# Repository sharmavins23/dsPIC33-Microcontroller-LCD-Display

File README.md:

# DSPIC33 Microcontroller with LCD Display

This project is a schematic and PCB layout of the dsPIC33 EP64 MC502
microcontroller, as well as an implementation of the LCD display and an LCD
display library.

## Schematic

The following is the circuit schematic.

## PCB Layout

The following is the PCB layout.

# License TL;DR

This project is distributed under the MIT license. This is a paraphrasing of a
[short summary](https://tldrlegal.com/license/mit-license).

This license is a short, permissive software license. Basically, you can do
whatever you want with this software, as long as you include the original
copyright and license notice in any copy of this software/source.

## What you CAN do:

-   You may commercially use this project in any way, and profit off it or the
    code included in any way;
-   You may modify or make changes to this project in any way;
-   You may distribute this project, the compiled code, or its source in any
    way;
-   You may incorporate this work into something that has a more restrictive
    license in any way;
-   And you may use the work for private use.

## What you CANNOT do:

-   You may not hold me (the author) liable for anything that happens to this
    code as well as anything that this code accomplishes. The work is provided
    as-is.

## What you MUST do:

-   You must include the copyright notice in all copies or substantial uses of
    the work;
-   You must include the license notice in all copies or substantial uses of the
    work.

If you're feeling generous, give credit to me somewhere in your projects.

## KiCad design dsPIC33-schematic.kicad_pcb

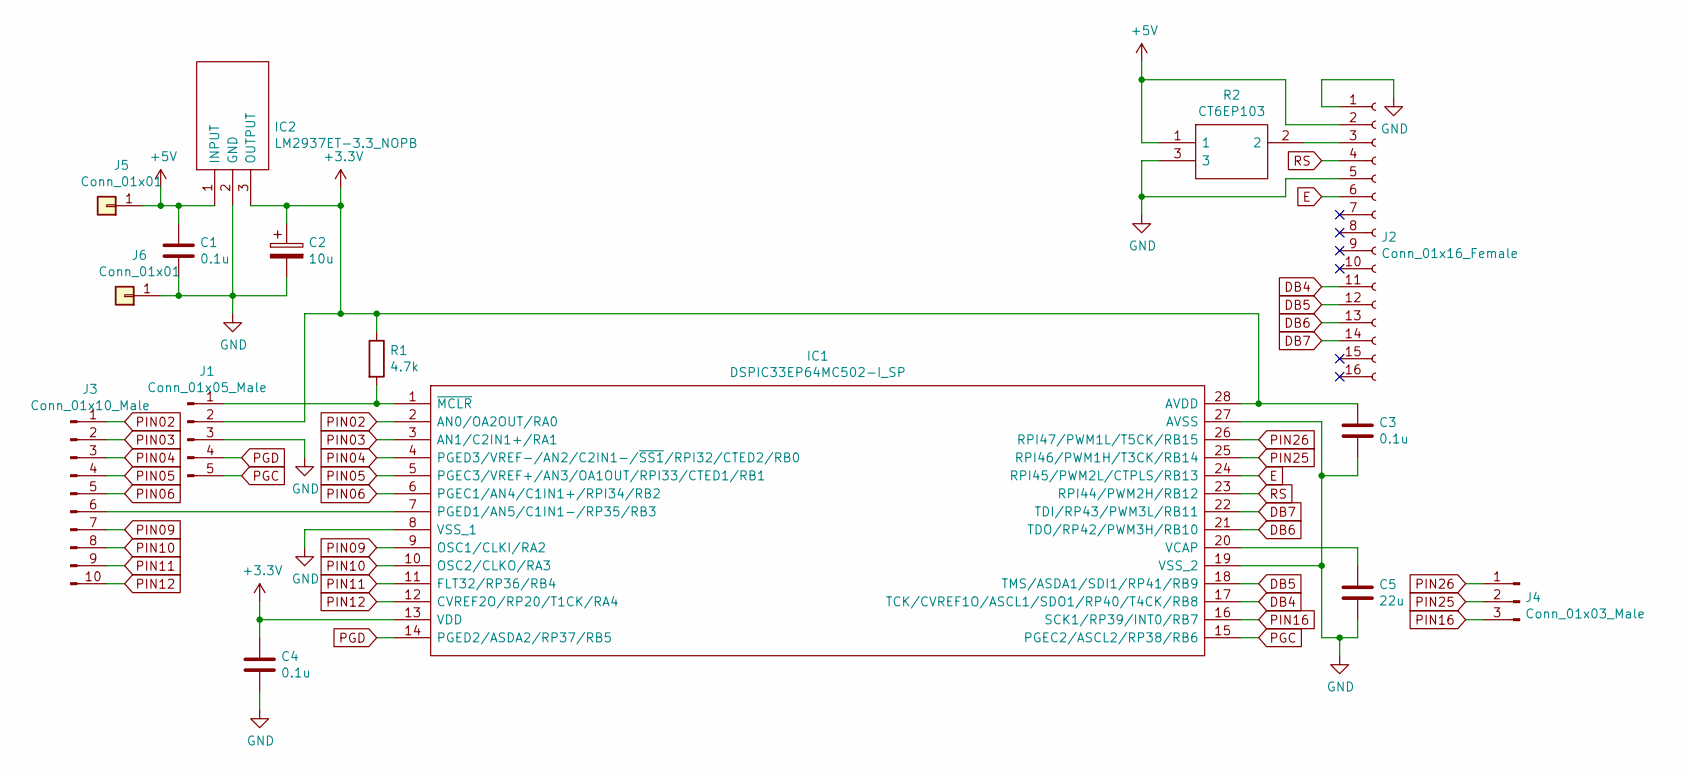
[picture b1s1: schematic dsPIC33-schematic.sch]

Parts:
C1, C3, C4: 0.1u; C_Disc_D5.0mm_W2.5mm_P2.50mm
C2: 10u; CP_Radial_D5.0mm_P2.00mm
C5: 22u; C_Disc_D5.0mm_W2.5mm_P2.50mm
IC1: DSPIC33EP64MC502-I_SP; DIP794W56P254L3486H508Q28N; Manufacturer_Part_Number DSPIC33EP64MC502-I/SP; Mouser Part Number 579-33EP64MC502ISP
IC2: LM2937ET-3.3_NOPB; TO254P470X1028X1955-3P; Manufacturer_Part_Number LM2937ET-3.3/NOPB; Mouser Part Number 926-LM2937ET-3.3NOPB
J1: Conn_01x05_Male; PinSocket_1x05_P2.54mm_Vertical
J2: Conn_01x16_Female; PinSocket_1x16_P2.54mm_Vertical
J3: Conn_01x10_Male; PinSocket_1x10_P2.54mm_Vertical
J4: Conn_01x03_Male; PinSocket_1x03_P2.54mm_Vertical
J5, J6: Conn_01x01; PinSocket_1x01_P2.54mm_Vertical
R1: 4.7k; R_Axial_DIN0207_L6.3mm_D2.5mm_P10.16mm_Horizontal
R2: CT6EP103; CT-6EP; Manufacturer_Part_Number CT6EP103

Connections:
+3V3: C2.1, C3.1, C4.1, IC1.13 (VDD), IC1.28 (AVDD), IC2.3 (OUTPUT), J1.2, R1.1
+5V: C1.1, IC2.1 (INPUT), J2.2, J5.1, R2.1
DB4: IC1.17 (TCK/CVREF1O/ASCL1/SDO1/RP40/T4CK/RB8), J2.11
DB5: IC1.18 (TMS/ASDA1/SDI1/RP41/RB9), J2.12
DB6: IC1.21 (TDO/RP42/PWM3H/RB10), J2.13
DB7: IC1.22 (TDI/RP43/PWM3L/RB11), J2.14
E: IC1.24 (RPI45/PWM2L/CTPLS/RB13), J2.6
GND: C1.2, C2.2, C3.2, C4.2, C5.2, IC1.8 (VSS_1), IC1.19 (VSS_2), IC1.27 (AVSS), IC2.2 (GND), J1.3, J2.1, J2.5, J6.1, R2.3
unnamed: C5.1, IC1.20 (VCAP)
unnamed: IC1.1 (~MCLR), J1.1, R1.2
unnamed: IC1.7 (PGED1/AN5/C1IN1-/RP35/RB3), J3.6
unnamed: J2.3, R2.2
PGC: IC1.15 (PGEC2/ASCL2/RP38/RB6), J1.5
PGD: IC1.14 (PGED2/ASDA2/RP37/RB5), J1.4
PIN02: IC1.2 (AN0/OA2OUT/RA0), J3.1
PIN03: IC1.3 (AN1/C2IN1+/RA1), J3.2
PIN04: IC1.4 (PGED3/VREF-/AN2/C2IN1-/~SS1~/RPI32/CTED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), J3.3
PIN05: IC1.5 (PGEC3/VREF+/AN3/OA1OUT/RPI33/CTED1/RB1), J3.4
PIN06: IC1.6 (PGEC1/AN4/C1IN1+/RPI34/RB2), J3.5
PIN09: IC1.9 (OSC1/CLKI/RA2), J3.7
PIN10: IC1.10 (OSC2/CLKO/RA3), J3.8
PIN11: IC1.11 (FLT32/RP36/RB4), J3.9
PIN12: IC1.12 (CVREF2O/RP20/T1CK/RA4), J3.10
PIN16: IC1.16 (SCK1/RP39/INT0/RB7), J4.3
PIN25: IC1.25 (RPI46/PWM1H/T3CK/RB14), J4.2
PIN26: IC1.26 (RPI47/PWM1L/T5CK/RB15), J4.1
RS: IC1.23 (RPI44/PWM2H/RB12), J2.4

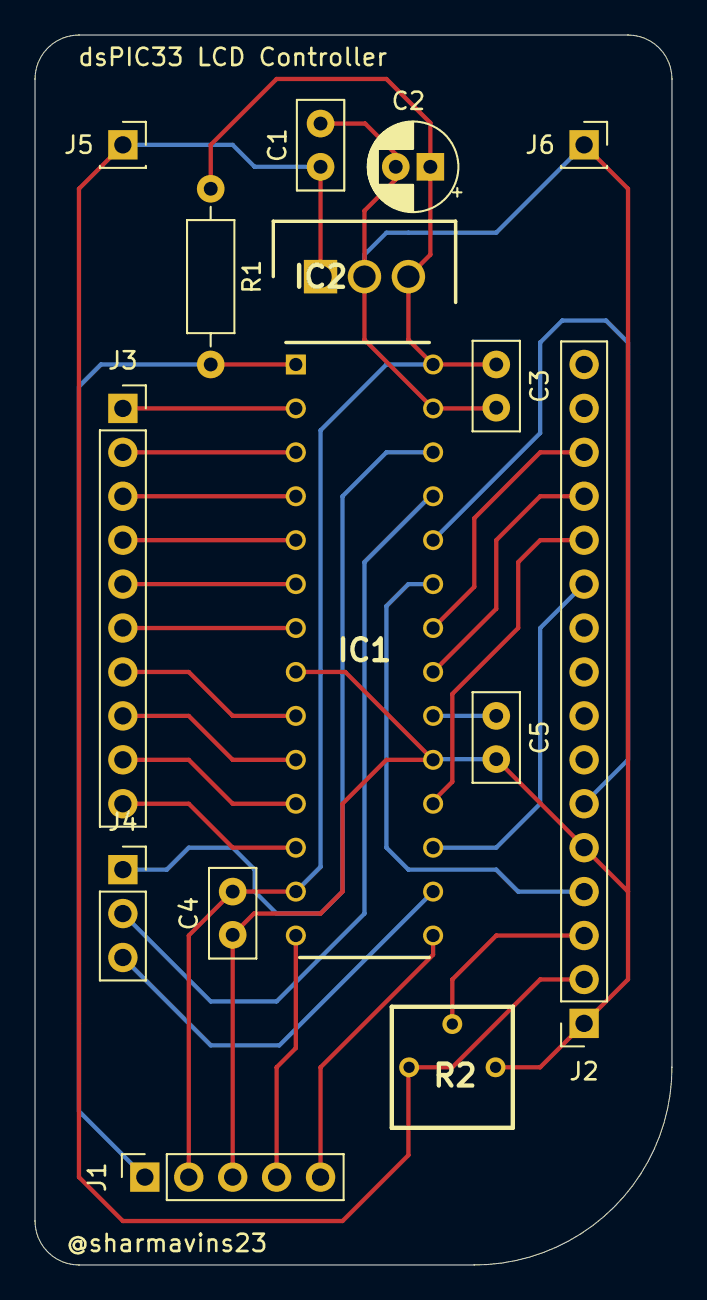
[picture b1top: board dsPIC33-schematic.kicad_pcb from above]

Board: 2 copper layers, 36.8 x 71.1 mm, 15 parts (0 on the bottom side), 27 nets.

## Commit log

2021-01-02 added title
2021-01-02 added LM2937 VReg
2021-01-02 added license
2021-01-02 added dsPIC
2021-01-02 added LCD module
2021-01-02 added 10k pot
2021-01-02 basic wiring setup complete
2021-01-02 updated schematic with netlist
2021-01-02 updated netlist with footprints
2021-01-02 added pcb design
2021-01-02 added PCB layout and gerber files
2021-01-02 moved gerber files
